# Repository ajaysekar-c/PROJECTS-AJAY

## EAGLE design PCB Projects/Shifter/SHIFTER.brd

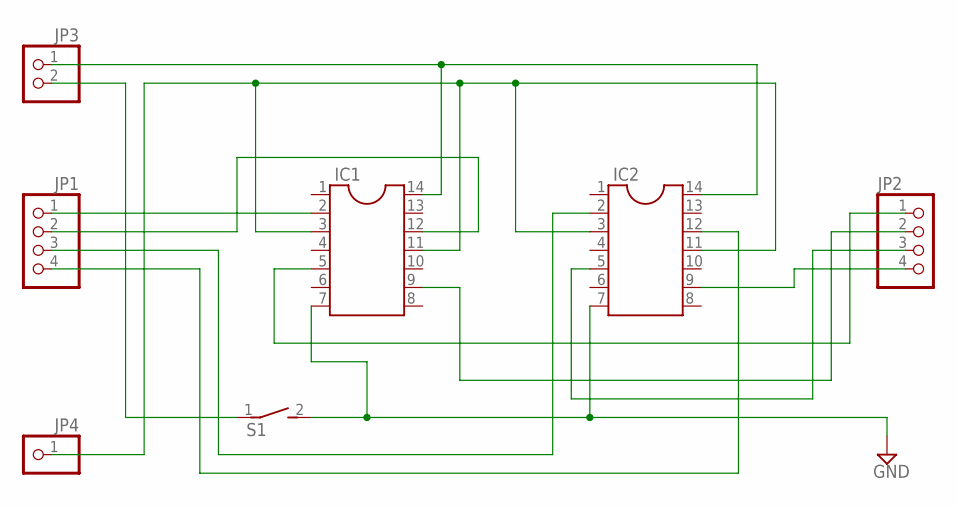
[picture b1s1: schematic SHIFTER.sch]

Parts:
IC1, IC2: DIL14
JP1, JP2: PINHD-1X4; 1X04
JP3: PINHD-1X2; 1X02
JP4: PINHD-1X1; 1X01
S1: DS01E; DS-01

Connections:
GND: IC1.7, IC2.7, S1.2
unnamed: IC1.5, JP2.1
unnamed: IC1.9, JP2.2
unnamed: IC2.5, JP2.3
unnamed: IC2.9, JP2.4
unnamed: IC1.2, JP1.1
unnamed: IC1.12, JP1.2
unnamed: IC2.2, JP1.3
unnamed: IC2.12, JP1.4
unnamed: IC1.3, IC1.11, IC2.3, IC2.11, JP4.1
unnamed: IC1.14, IC2.14, JP3.1
unnamed: JP3.2, S1.1

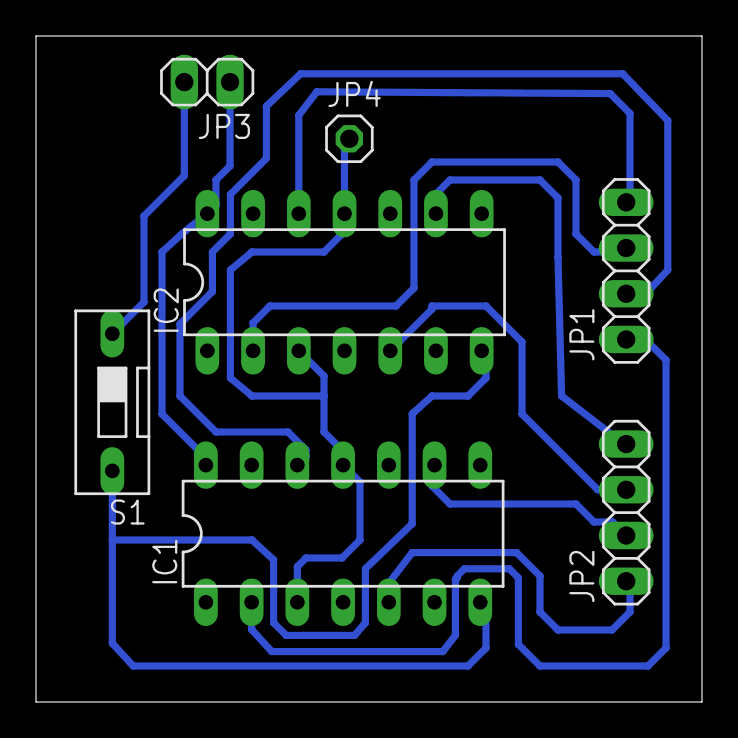
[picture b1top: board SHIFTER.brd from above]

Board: 2 copper layers, 37.0 x 37.0 mm, 7 parts (0 on the bottom side), 12 nets.

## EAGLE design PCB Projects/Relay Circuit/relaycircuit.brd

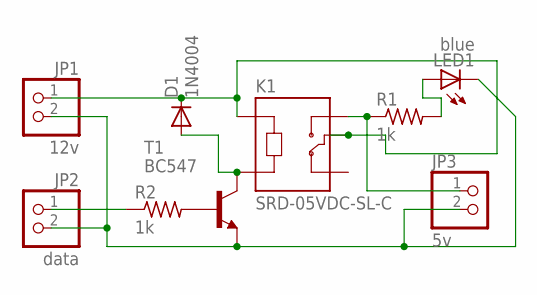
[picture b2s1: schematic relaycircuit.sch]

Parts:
D1: 1N4004; DO41-10
JP1: 12v; 1X02
JP2: data; 1X02
JP3: 5v; 1X02
K1: SRD-05VDC-SL-C; RELAY_SRD-05VDC-SL-C
LED1: blue; LED5MM
R1, R2: 1k; 0207/10
T1: BC547; TO92

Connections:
unnamed: JP3.1, K1.NO, R1.1
unnamed: R2.2, T1.2 (B)
unnamed: D1.A, K1.A2, T1.3 (C)
unnamed: LED1.A, R1.2
unnamed: JP1.2, JP2.2, JP3.2, LED1.K (C), T1.1 (E)
unnamed: JP2.1, R2.1
unnamed: D1.C, JP1.1, K1.A1, K1.COM

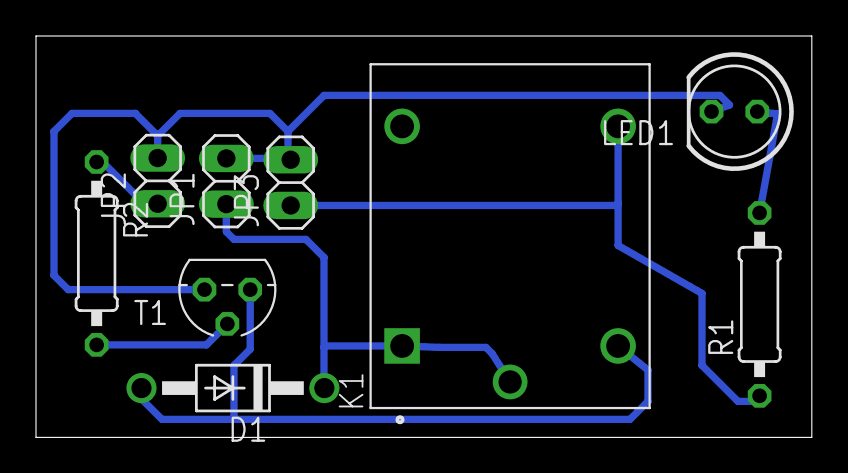
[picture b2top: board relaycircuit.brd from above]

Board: 2 copper layers, 43.1 x 22.3 mm, 9 parts (0 on the bottom side), 7 nets.

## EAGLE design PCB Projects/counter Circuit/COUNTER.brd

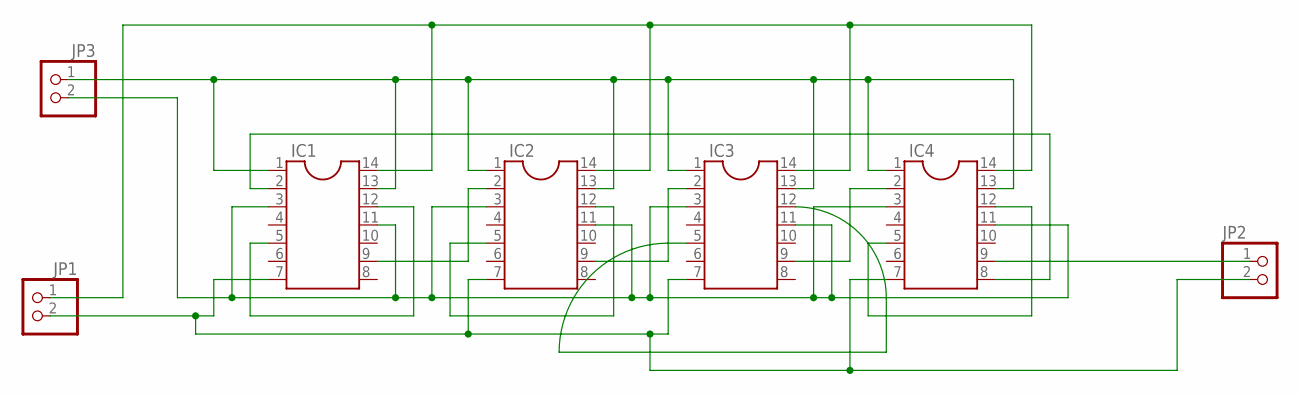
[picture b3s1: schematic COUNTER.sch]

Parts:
IC1, IC2, IC3, IC4: DIL14
JP1, JP2, JP3: PINHD-1X2; 1X02

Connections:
unnamed: IC1.3, IC1.11, IC2.3, IC2.11, IC3.3, IC3.11, IC4.3, IC4.11, JP3.2
unnamed: IC1.2, IC4.8
unnamed: IC1.5, IC1.12
unnamed: IC1.9, IC2.2
unnamed: IC2.5, IC2.12
unnamed: IC2.9, IC3.2
unnamed: IC3.5, IC3.12
unnamed: IC3.9, IC4.2
unnamed: IC4.5, IC4.12
unnamed: IC1.1, IC1.13, IC2.1, IC2.13, IC3.1, IC3.13, IC4.1, IC4.13, JP3.1
unnamed: IC1.14, IC2.14, IC3.14, IC4.14, JP1.1
unnamed: IC1.7, IC2.7, IC3.7, IC4.7, JP1.2, JP2.2
unnamed: IC4.9, JP2.1

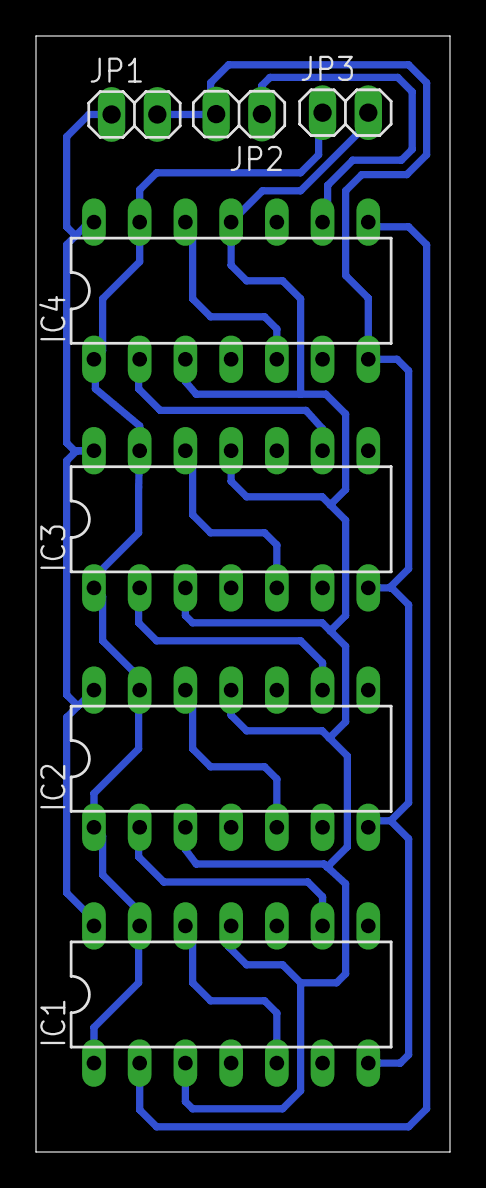
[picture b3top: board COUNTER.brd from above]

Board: 2 copper layers, 23.0 x 62.0 mm, 7 parts (0 on the bottom side), 13 nets.

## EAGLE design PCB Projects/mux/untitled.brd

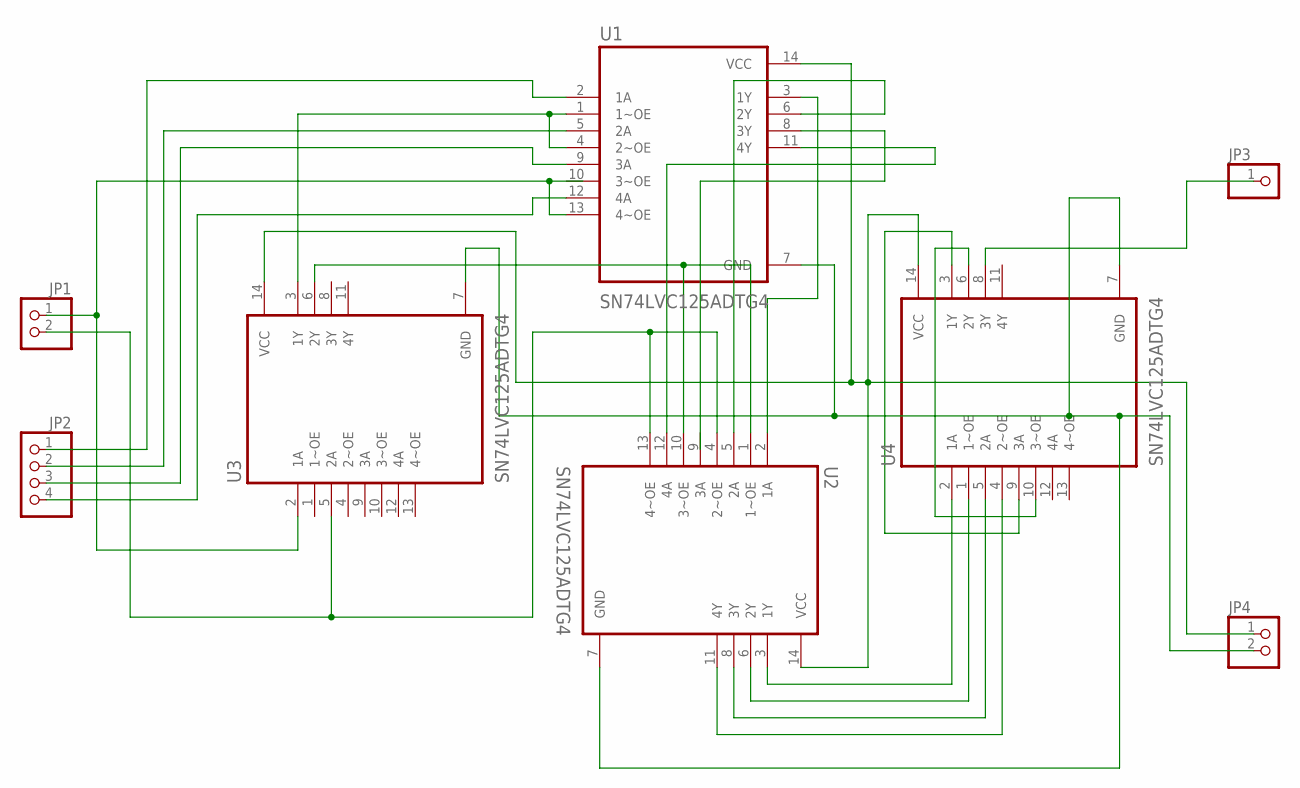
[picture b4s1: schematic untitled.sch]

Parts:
JP1, JP4: PINHD-1X2; 1X02
JP2: PINHD-1X4; 1X04
JP3: PINHD-1X1; 1X01
U1, U2, U3, U4: SN74LVC125ADTG4; SOIC127P600X175-14N

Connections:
unnamed: JP4.1, U1.14 (VCC), U2.14 (VCC), U3.14 (VCC), U4.14 (VCC)
unnamed: JP2.3, U1.9 (3A)
unnamed: JP2.4, U1.12 (4A)
unnamed: JP1.1, U1.13 (4~OE), U3.2 (1A)
unnamed: JP4.2, U1.7 (GND), U2.7 (GND), U3.7 (GND), U4.7 (GND)
unnamed: JP2.1, U1.2 (1A)
unnamed: JP2.2, U1.5 (2A)
unnamed: U1.1 (1~OE), U1.4 (2~OE), U3.3 (1Y)
unnamed: U1.3 (1Y), U2.2 (1A)
unnamed: U1.6 (2Y), U2.5 (2A)
unnamed: U1.11 (4Y), U2.12 (4A)
unnamed: JP1.2, U2.4 (2~OE), U2.13 (4~OE), U3.5 (2A)
unnamed: U2.1 (1~OE), U2.10 (3~OE), U3.6 (2Y)
unnamed: U2.3 (1Y), U4.2 (1A)
unnamed: U2.6 (2Y), U4.1 (1~OE)
unnamed: U2.8 (3Y), U4.5 (2A)
unnamed: U2.11 (4Y), U4.4 (2~OE)
unnamed: U4.3 (1Y), U4.9 (3A)
unnamed: U4.6 (2Y), U4.10 (3~OE)
unnamed: JP3.1, U4.8 (3Y)

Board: 2 copper layers, 8 parts (0 on the bottom side), 20 nets, no tracks yet.

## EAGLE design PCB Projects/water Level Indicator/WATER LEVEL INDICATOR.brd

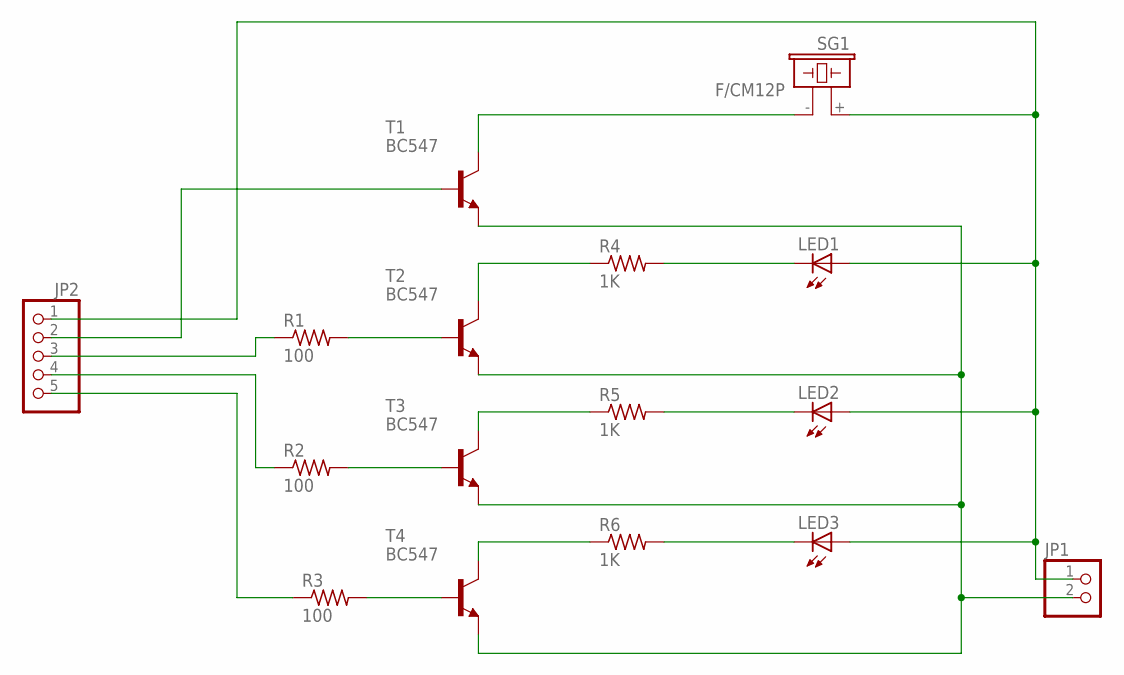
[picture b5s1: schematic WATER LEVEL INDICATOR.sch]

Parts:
JP1: PINHD-1X2; 1X02
JP2: PINHD-1X5; 1X05
LED1, LED2, LED3: LED5MM
R1, R2, R3: 100; 0207/10
R4, R5, R6: 1K; 0207/10
SG1: F/CM12P
T1, T2, T3, T4: BC547; TO92

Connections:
unnamed: LED1.K (C), R4.2
unnamed: JP2.2, T1.2 (B)
unnamed: SG1.- (2), T1.3 (C)
unnamed: JP2.3, R1.1
unnamed: R1.2, T2.2 (B)
unnamed: R4.1, T2.3 (C)
unnamed: LED2.K (C), R5.2
unnamed: JP2.4, R2.1
unnamed: R2.2, T3.2 (B)
unnamed: R5.1, T3.3 (C)
unnamed: LED3.K (C), R6.2
unnamed: JP1.1, JP2.1, LED1.A, LED2.A, LED3.A, SG1.+ (1)
unnamed: JP2.5, R3.1
unnamed: R3.2, T4.2 (B)
unnamed: R6.1, T4.3 (C)
unnamed: JP1.2, T1.1 (E), T2.1 (E), T3.1 (E), T4.1 (E)

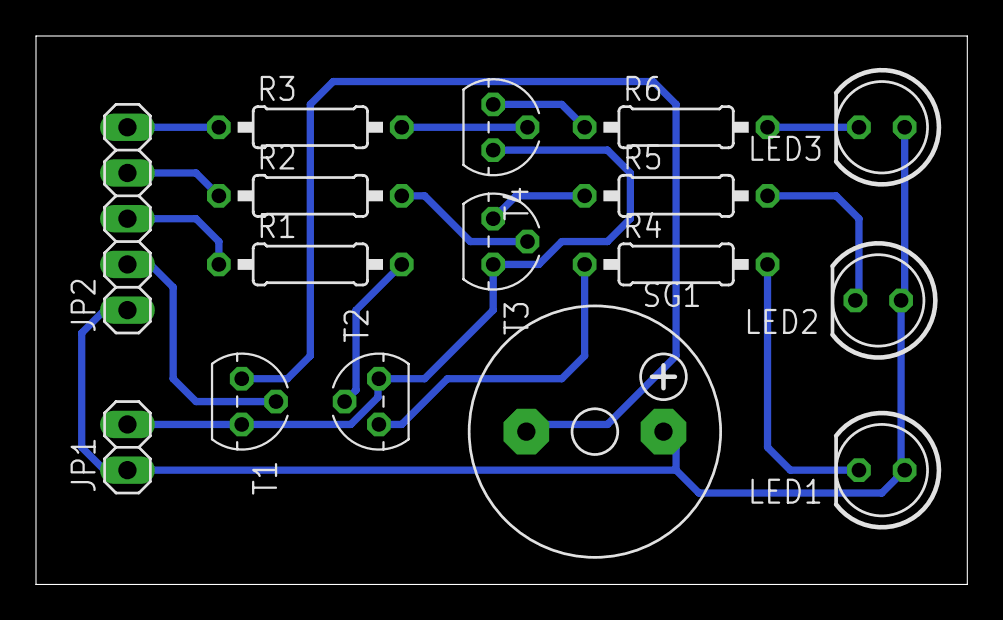
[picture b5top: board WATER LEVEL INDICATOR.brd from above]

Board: 2 copper layers, 51.7 x 30.5 mm, 16 parts (0 on the bottom side), 16 nets.

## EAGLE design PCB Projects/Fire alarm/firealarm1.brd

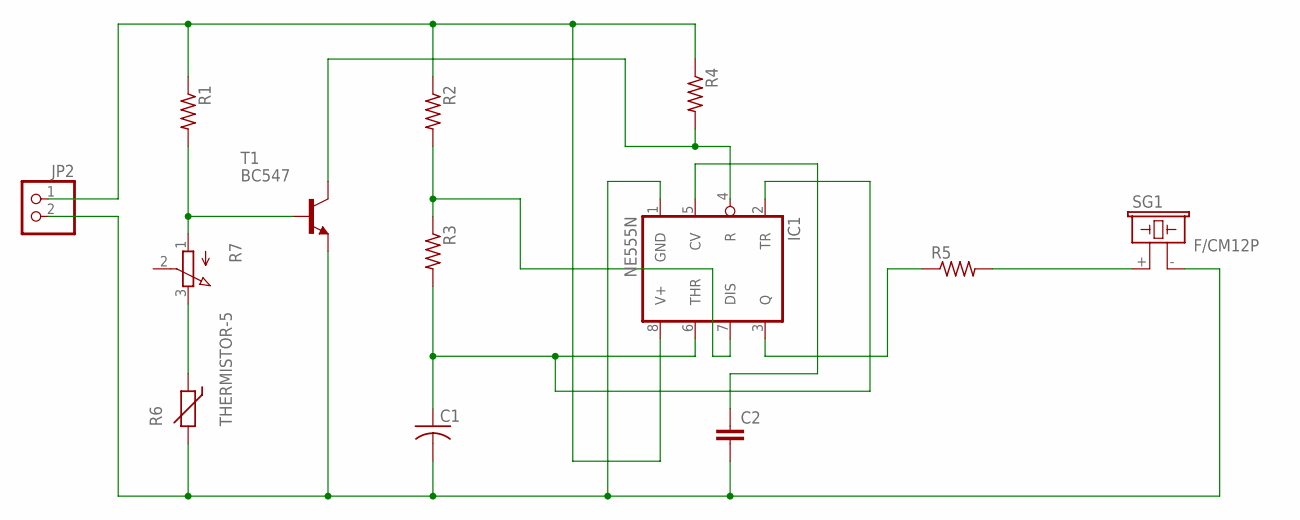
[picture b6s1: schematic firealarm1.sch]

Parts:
C1: C-US050-025X075; C050-025X075
C2: C-EU025-025X050; C025-025X050
IC1: NE555N; DIL08
JP2: PINHD-1X2; 1X02
R1, R2, R3, R4, R5: R-US_0207/10; 0207/10
R6: THERMISTOR-5; R-5
R7: 3RP/1610N
SG1: F/CM12P
T1: BC547; TO92

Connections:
unnamed: IC1.8 (V+), JP2.1, R1.1, R2.1, R4.1
unnamed: C1.2, C2.2, IC1.1 (GND), JP2.2, R6.2, SG1.- (2), T1.1 (E)
unnamed: C2.1, IC1.5 (CV)
unnamed: IC1.7 (DIS), R2.2, R3.1
unnamed: IC1.3 (Q), R5.1
unnamed: R5.2, SG1.+ (1)
unnamed: C1.1, IC1.2 (TR), IC1.6 (THR), R3.2
unnamed: IC1.4 (R), R4.2, T1.3 (C)
unnamed: R1.2, R7.1 (A), T1.2 (B)
unnamed: R6.1, R7.3 (E)

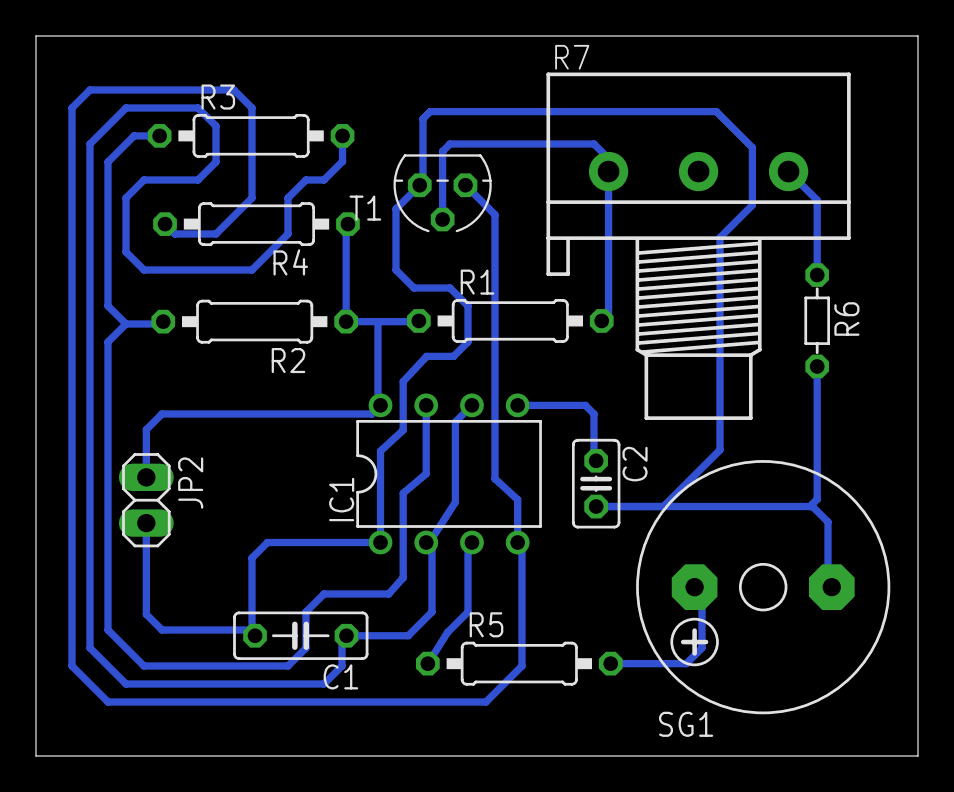
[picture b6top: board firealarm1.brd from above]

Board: 2 copper layers, 49.0 x 40.0 mm, 13 parts (0 on the bottom side), 10 nets.

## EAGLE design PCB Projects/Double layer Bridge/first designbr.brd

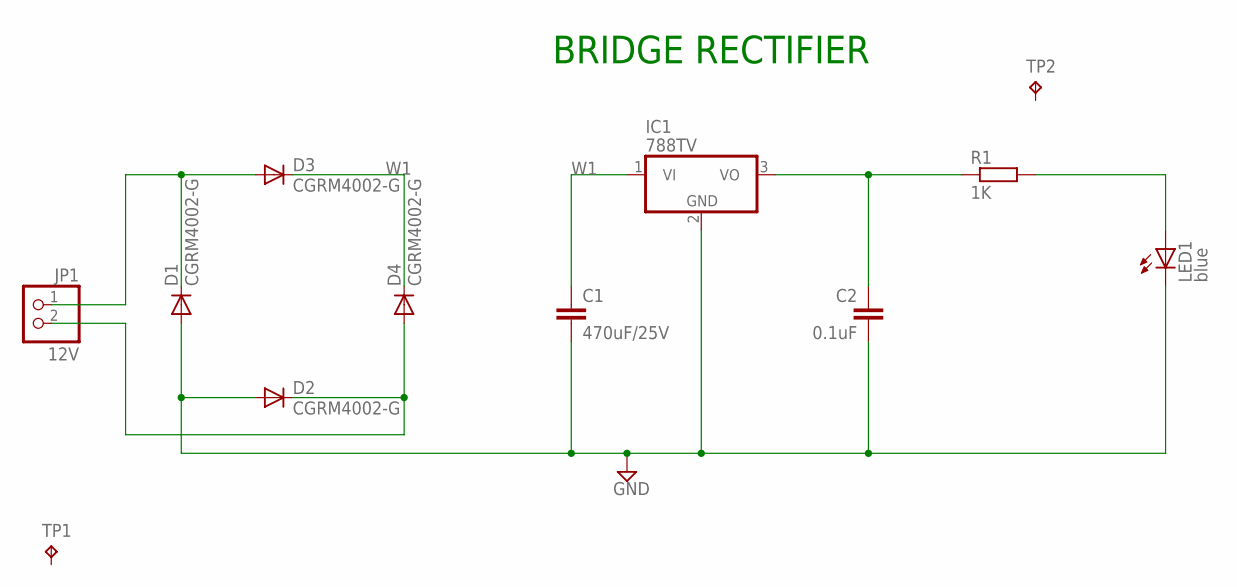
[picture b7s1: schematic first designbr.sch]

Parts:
C1: 470uF/25V; C1206
C2: 0.1uF; C1206
D1, D2, D3, D4: CGRM4002-G; SOD323-W
IC1: 788TV; TO220V
JP1: 12V; 1X02
LED1: blue; LED5MM
R1: 1K; M0805
TP1, TP2: TPTP11R; TP11R

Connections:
GND: C1.2, C2.2, D1.A, D2.A, IC1.2 (GND), LED1.K (C)
unnamed: D1.C, D3.A, JP1.1
unnamed: D2.C, D4.A, JP1.2
unnamed: C2.1, IC1.3 (VO), R1.1
unnamed: LED1.A, R1.2
W1: C1.1, D3.C, D4.C, IC1.1 (VI)

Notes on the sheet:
BRIDGE RECTIFIER

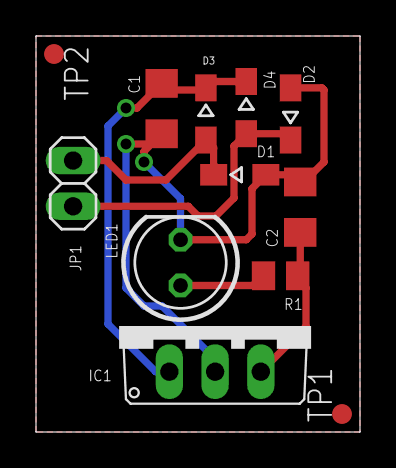
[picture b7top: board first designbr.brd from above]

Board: 2 copper layers, 18.0 x 22.0 mm, 12 parts (0 on the bottom side), 6 nets.

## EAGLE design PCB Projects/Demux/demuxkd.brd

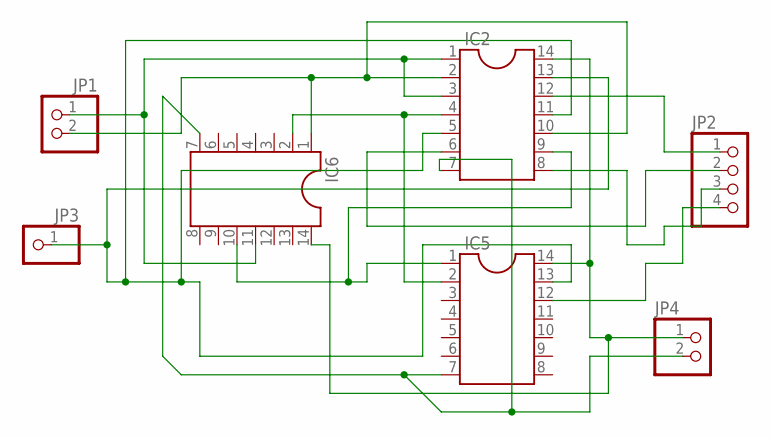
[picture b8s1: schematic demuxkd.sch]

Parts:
IC2, IC5, IC6: DIL14
JP1, JP4: PINHD-1X2; 1X02
JP2: PINHD-1X4; 1X04
JP3: PINHD-1X1; 1X01

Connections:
unnamed: IC2.1, IC2.3, IC6.11, JP1.1
unnamed: IC2.9, IC5.1, IC6.10
unnamed: IC2.2, IC2.10, IC6.1, JP1.2
unnamed: IC2.5, IC2.11, IC2.13, IC5.13, JP3.1
unnamed: IC2.4, IC5.2, IC6.2
unnamed: IC2.7, IC5.7, IC6.7, JP4.2
unnamed: IC2.12, JP2.1
unnamed: IC2.6, JP2.2
unnamed: IC2.8, JP2.3
unnamed: IC5.12, JP2.4
unnamed: IC2.14, IC5.14, IC6.14, JP4.1

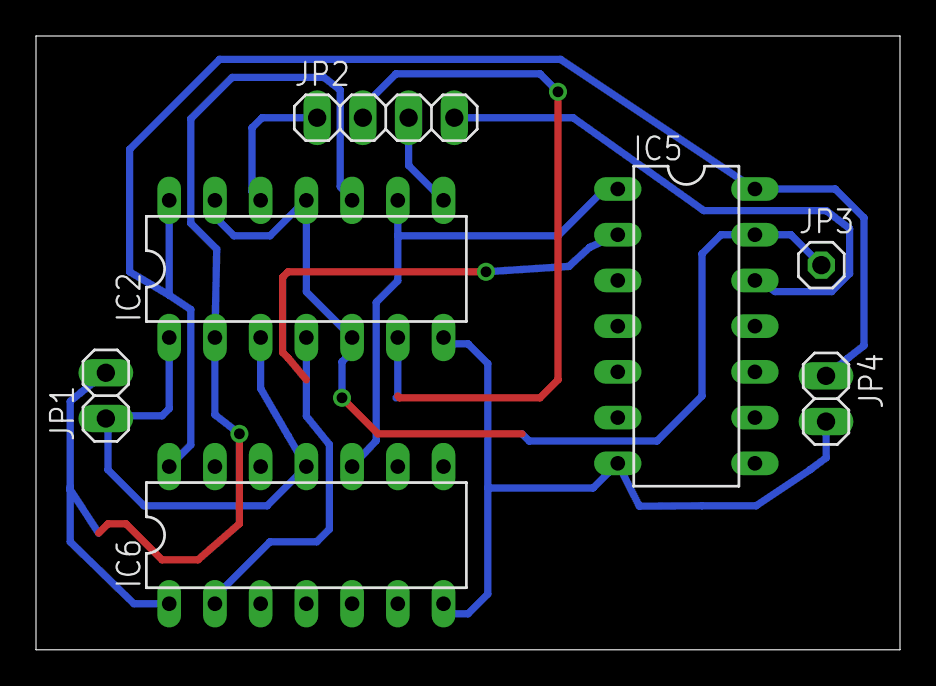
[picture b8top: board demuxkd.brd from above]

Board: 2 copper layers, 48.0 x 34.1 mm, 7 parts (0 on the bottom side), 11 nets.

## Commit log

2025-03-09 Create temp
2025-03-09 Create IBM Main Project
2025-03-09 Create IBM Main Project (ROAD)
